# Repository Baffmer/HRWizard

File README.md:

# HRWizard
Projekt "HRWizard" für das Modul "Eingebettete Systeme"

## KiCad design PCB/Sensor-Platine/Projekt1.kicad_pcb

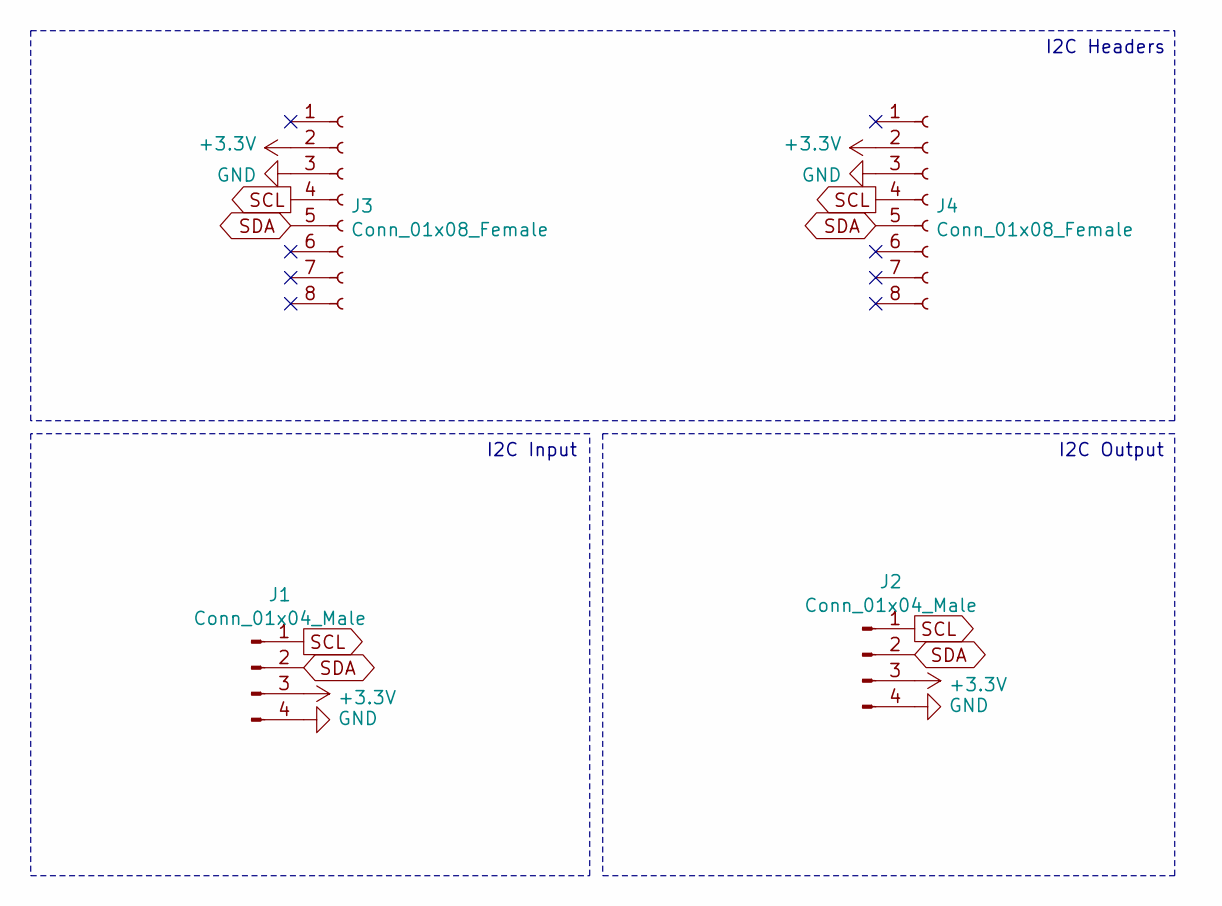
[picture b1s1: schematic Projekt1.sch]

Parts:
J1, J2: Conn_01x04_Male; PinHeader_1x04_P2.00mm_Vertical
J3, J4: Conn_01x08_Female; PinHeader_1x08_P2.54mm_Vertical

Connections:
+3V3: J1.3, J2.3, J3.2, J4.2
GND: J1.4, J2.4, J3.3, J4.3
SCL: J1.1, J2.1, J3.4, J4.4
SDA: J1.2, J2.2, J3.5, J4.5

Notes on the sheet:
I2C Input
I2C Output
I2C Headers

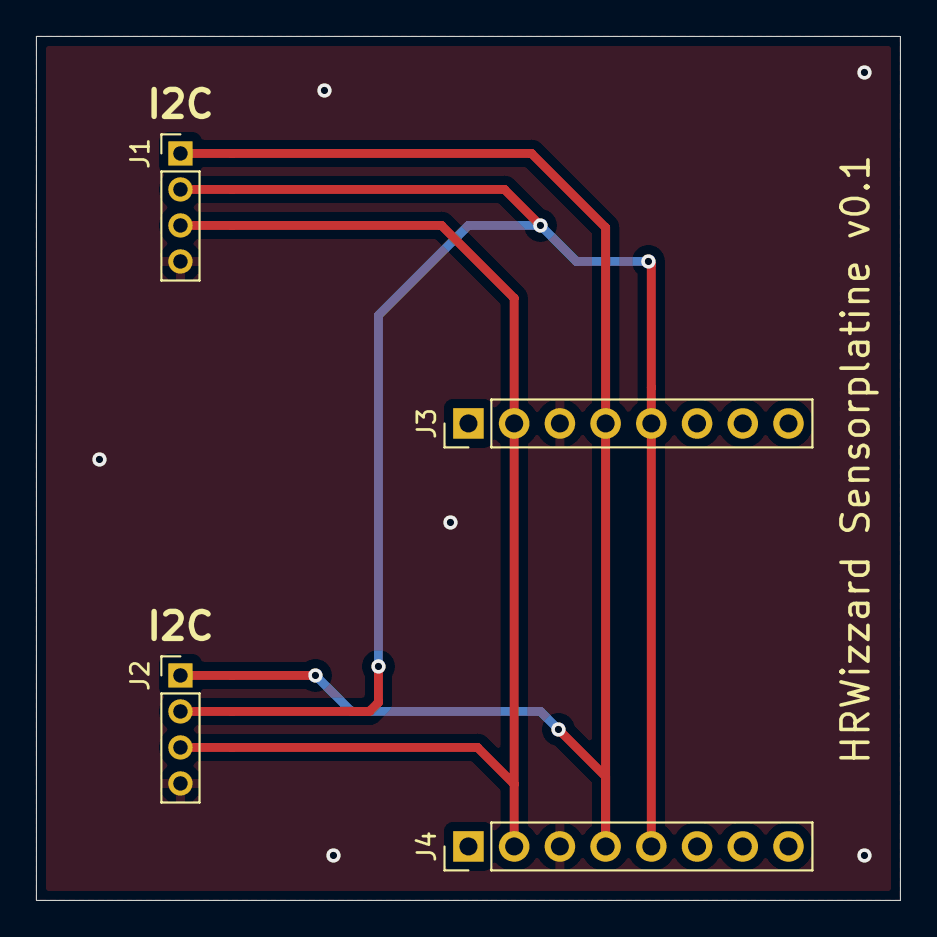
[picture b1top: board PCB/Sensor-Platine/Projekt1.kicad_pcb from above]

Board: 2 copper layers, 48.0 x 48.0 mm, 4 parts (0 on the bottom side), 4 nets.

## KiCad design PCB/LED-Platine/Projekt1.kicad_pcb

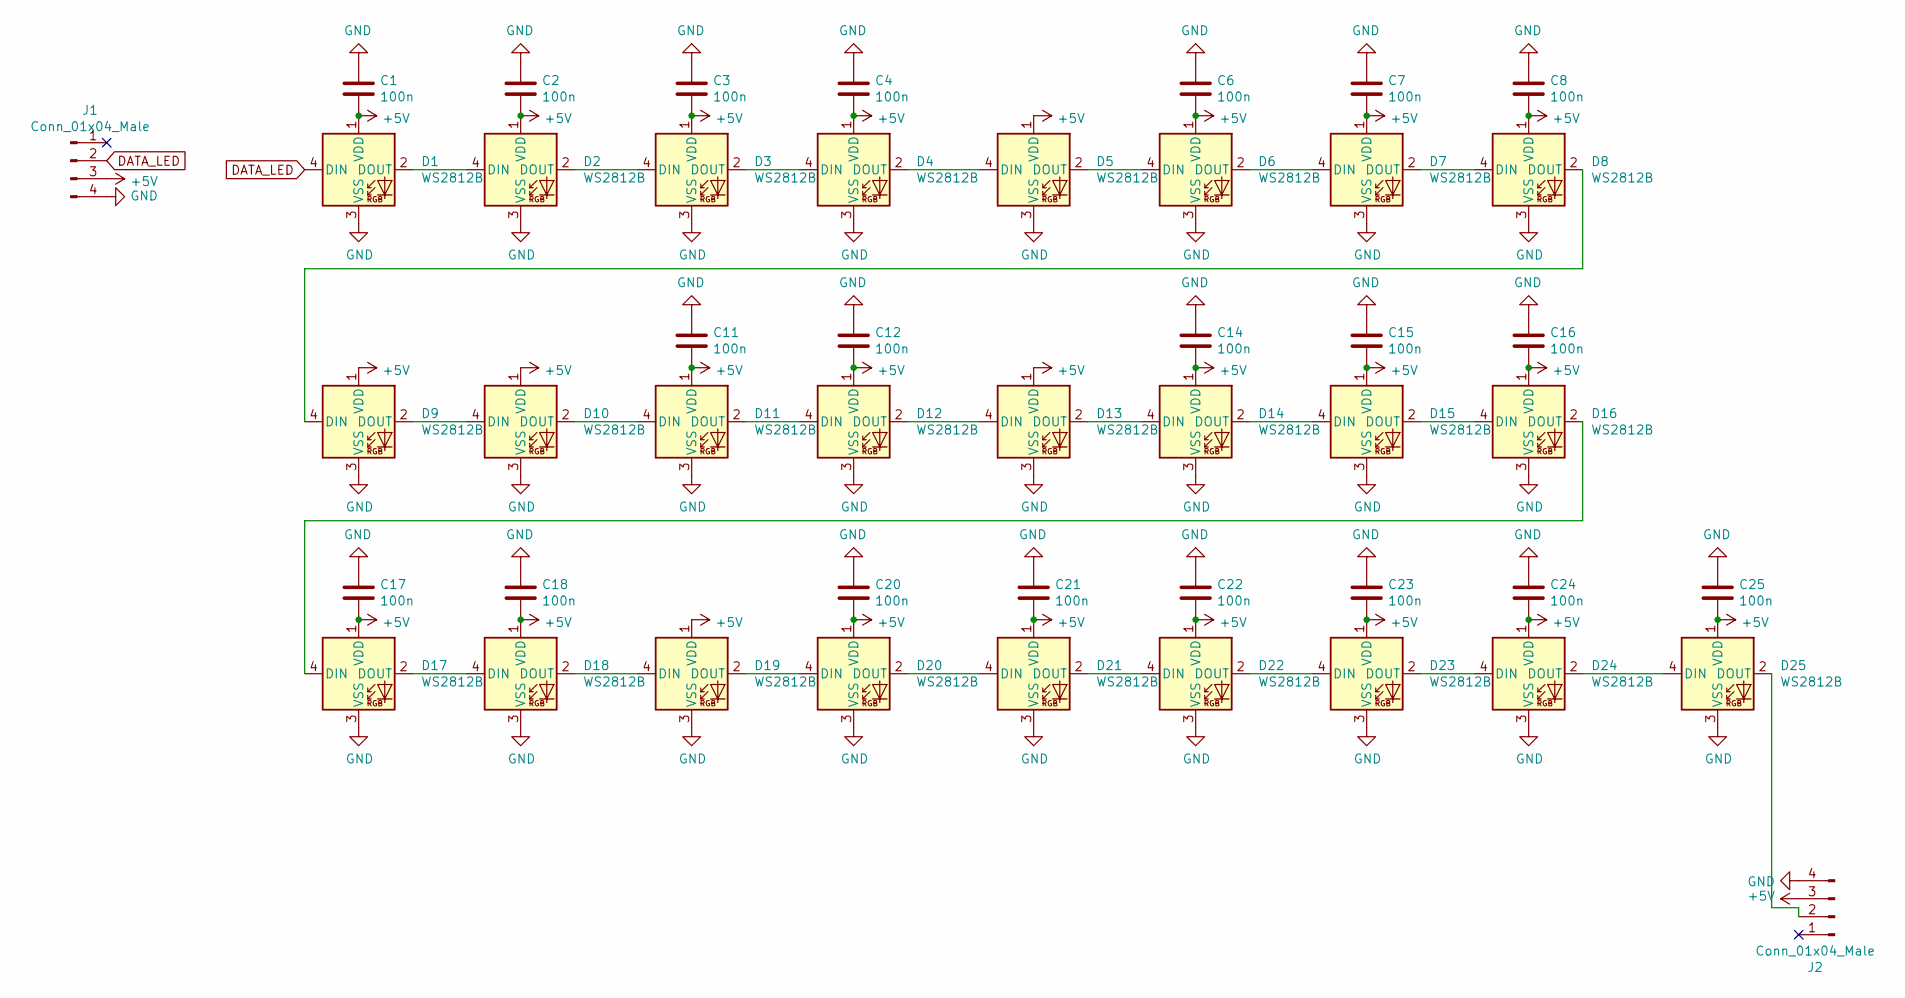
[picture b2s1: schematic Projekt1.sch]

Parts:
C1, C2, C3, C4, C6, C7, C8, C11, C12, C14, C15, C16, C17, C18, C20, C21, C22, C23, C24, C25: 100n; C_0805_2012Metric_Pad1.18x1.45mm_HandSolder
D1, D2, D3, D4, D5, D6, D7, D8, D9, D10, D11, D12, D13, D14, D15, D16, D17, D18, D19, D20, D21, D22, D23, D24, D25: WS2812B; LED_WS2812B_PLCC4_5.0x5.0mm_P3.2mm
J1, J2: Conn_01x04_Male; PinHeader_1x04_P2.00mm_Vertical

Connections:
+5V: C1.1, C2.1, C3.1, C4.1, C6.1, C7.1, C8.1, C11.1, C12.1, C14.1, C15.1, C16.1, C17.1, C18.1, C20.1, C21.1, C22.1, C23.1, C24.1, C25.1, D1.1 (VDD), D2.1 (VDD), D3.1 (VDD), D4.1 (VDD), D5.1 (VDD), D6.1 (VDD), D7.1 (VDD), D8.1 (VDD), D9.1 (VDD), D10.1 (VDD), D11.1 (VDD), D12.1 (VDD), D13.1 (VDD), D14.1 (VDD), D15.1 (VDD), D16.1 (VDD), D17.1 (VDD), D18.1 (VDD), D19.1 (VDD), D20.1 (VDD), D21.1 (VDD), D22.1 (VDD), D23.1 (VDD), D24.1 (VDD), D25.1 (VDD), J1.3, J2.3
DATA_LED: D1.4 (DIN), J1.2
GND: C1.2, C2.2, C3.2, C4.2, C6.2, C7.2, C8.2, C11.2, C12.2, C14.2, C15.2, C16.2, C17.2, C18.2, C20.2, C21.2, C22.2, C23.2, C24.2, C25.2, D1.3 (VSS), D2.3 (VSS), D3.3 (VSS), D4.3 (VSS), D5.3 (VSS), D6.3 (VSS), D7.3 (VSS), D8.3 (VSS), D9.3 (VSS), D10.3 (VSS), D11.3 (VSS), D12.3 (VSS), D13.3 (VSS), D14.3 (VSS), D15.3 (VSS), D16.3 (VSS), D17.3 (VSS), D18.3 (VSS), D19.3 (VSS), D20.3 (VSS), D21.3 (VSS), D22.3 (VSS), D23.3 (VSS), D24.3 (VSS), D25.3 (VSS), J1.4, J2.4
unnamed: D1.2 (DOUT), D2.4 (DIN)
unnamed: D2.2 (DOUT), D3.4 (DIN)
unnamed: D3.2 (DOUT), D4.4 (DIN)
unnamed: D4.2 (DOUT), D5.4 (DIN)
unnamed: D5.2 (DOUT), D6.4 (DIN)
unnamed: D6.2 (DOUT), D7.4 (DIN)
unnamed: D7.2 (DOUT), D8.4 (DIN)
unnamed: D8.2 (DOUT), D9.4 (DIN)
unnamed: D10.2 (DOUT), D11.4 (DIN)
unnamed: D9.2 (DOUT), D10.4 (DIN)
unnamed: D11.2 (DOUT), D12.4 (DIN)
unnamed: D12.2 (DOUT), D13.4 (DIN)
unnamed: D13.2 (DOUT), D14.4 (DIN)
unnamed: D14.2 (DOUT), D15.4 (DIN)
unnamed: D15.2 (DOUT), D16.4 (DIN)
unnamed: D16.2 (DOUT), D17.4 (DIN)
unnamed: D17.2 (DOUT), D18.4 (DIN)
unnamed: D18.2 (DOUT), D19.4 (DIN)
unnamed: D19.2 (DOUT), D20.4 (DIN)
unnamed: D20.2 (DOUT), D21.4 (DIN)
unnamed: D21.2 (DOUT), D22.4 (DIN)
unnamed: D22.2 (DOUT), D23.4 (DIN)
unnamed: D23.2 (DOUT), D24.4 (DIN)
unnamed: D24.2 (DOUT), D25.4 (DIN)
unnamed: D25.2 (DOUT), J2.2

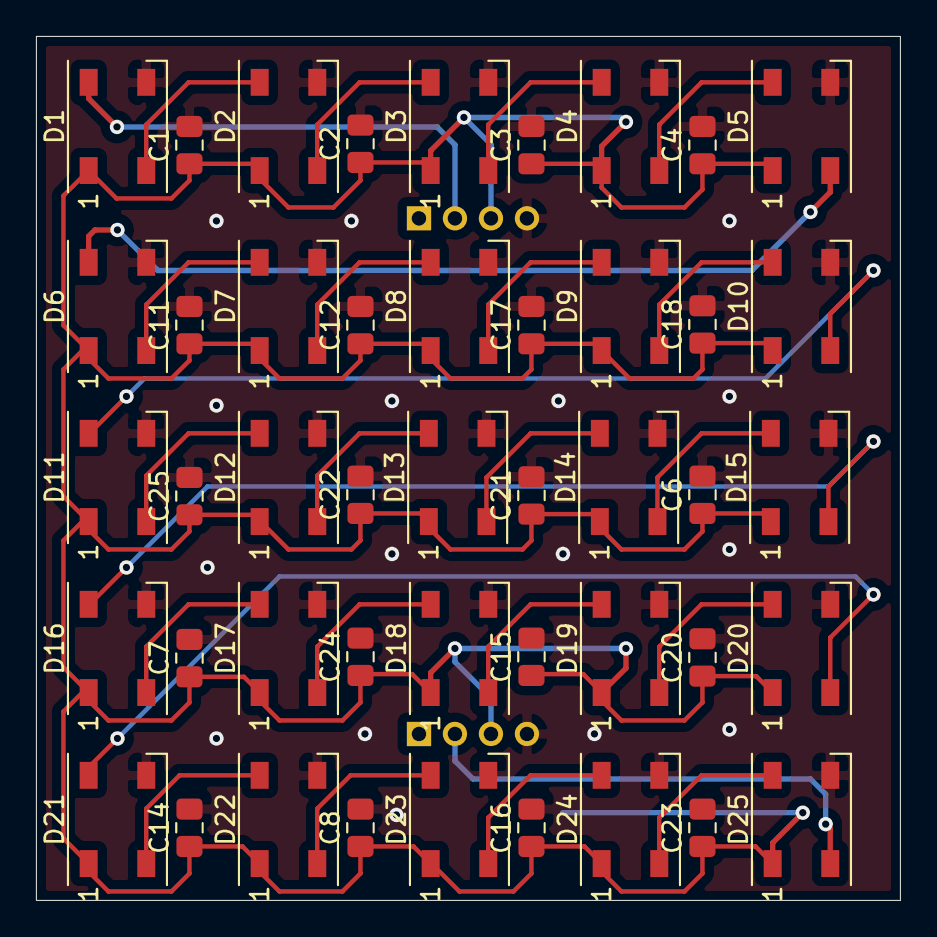
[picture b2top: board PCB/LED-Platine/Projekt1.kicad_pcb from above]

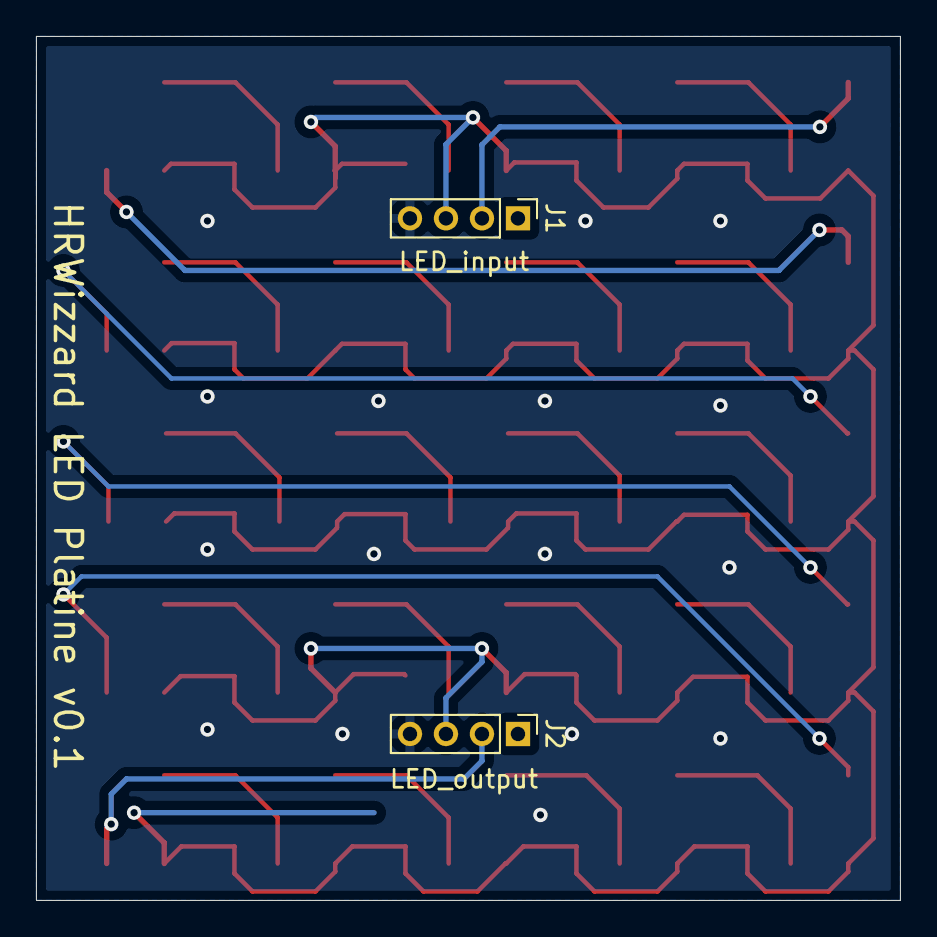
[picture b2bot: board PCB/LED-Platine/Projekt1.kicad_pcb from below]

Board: 2 copper layers, 48.0 x 48.0 mm, 47 parts (2 on the bottom side), 28 nets.

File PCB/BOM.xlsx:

Name | MPN | Placed | References | Value | Quantity PCB | Quantity | Price Per Piece | Price
Seeed Studio Zubehör Grove - Universal 4 pin connector | 110990030 | yes | Grove Stecker | Grove_Connector | 3 | 7 | 0.127 | 2.6669999999999998
Female Pin Header für Sensoren | M20-7820842 | yes | Sensorplatine | Conn_01x08_Female | 3 | 2 | 0.88900000000000001 | 5.3339999999999996
Pufferkondensator für LEDs | CC0805KRX7R9BB104 | yes | C1, C2, C3, C4, C6, C7, C8, C11, C12, C14, C15, C16, C17, C18, C20, C21, C22, C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 | 0805 - 100n | 3 | 20 | 3.3000000000000002E-2 | 1.98
RGB LEDs | COM-16346 | yes | D1, D2, D3, D4, D5, D6, D7, D8, D9, D10, D11, D12, D13, D14, D15, D16, D17, D18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 | WS2812B | 3 | 25 | 0.44040000000000001 | 33.03
Vorwiderstand Power LED | CRCW0805330RFKTA | yes | R9 | 0805 - 330R | 3 | 1 | 0.108 | 0.32400000000000001
Power LED orange | HSMD-C170 | yes | D1 | LED_Small | 3 | 1 | 0.219 | 0.65700000000000003
Raspberry Pi Pico | DEV-17829 | yes | U1 | Pico | 3 | 1 | 4.29 | 12.870000000000001
Tactical Switch | TS04-66-95-BK-260-SMT | yes | SW1, SW2, SW3, SW4, SW5, SW6, SW7 | SW_Push | 3 | 7 | 0.14699999999999999 | 3.0869999999999997
Seeed Grove Cable | 114991495 |  |  |  | 1 | 20 | 0.47 | 9.3999999999999986
 |  |  |  |  |  |  | Gesamt: | 69.349000000000018

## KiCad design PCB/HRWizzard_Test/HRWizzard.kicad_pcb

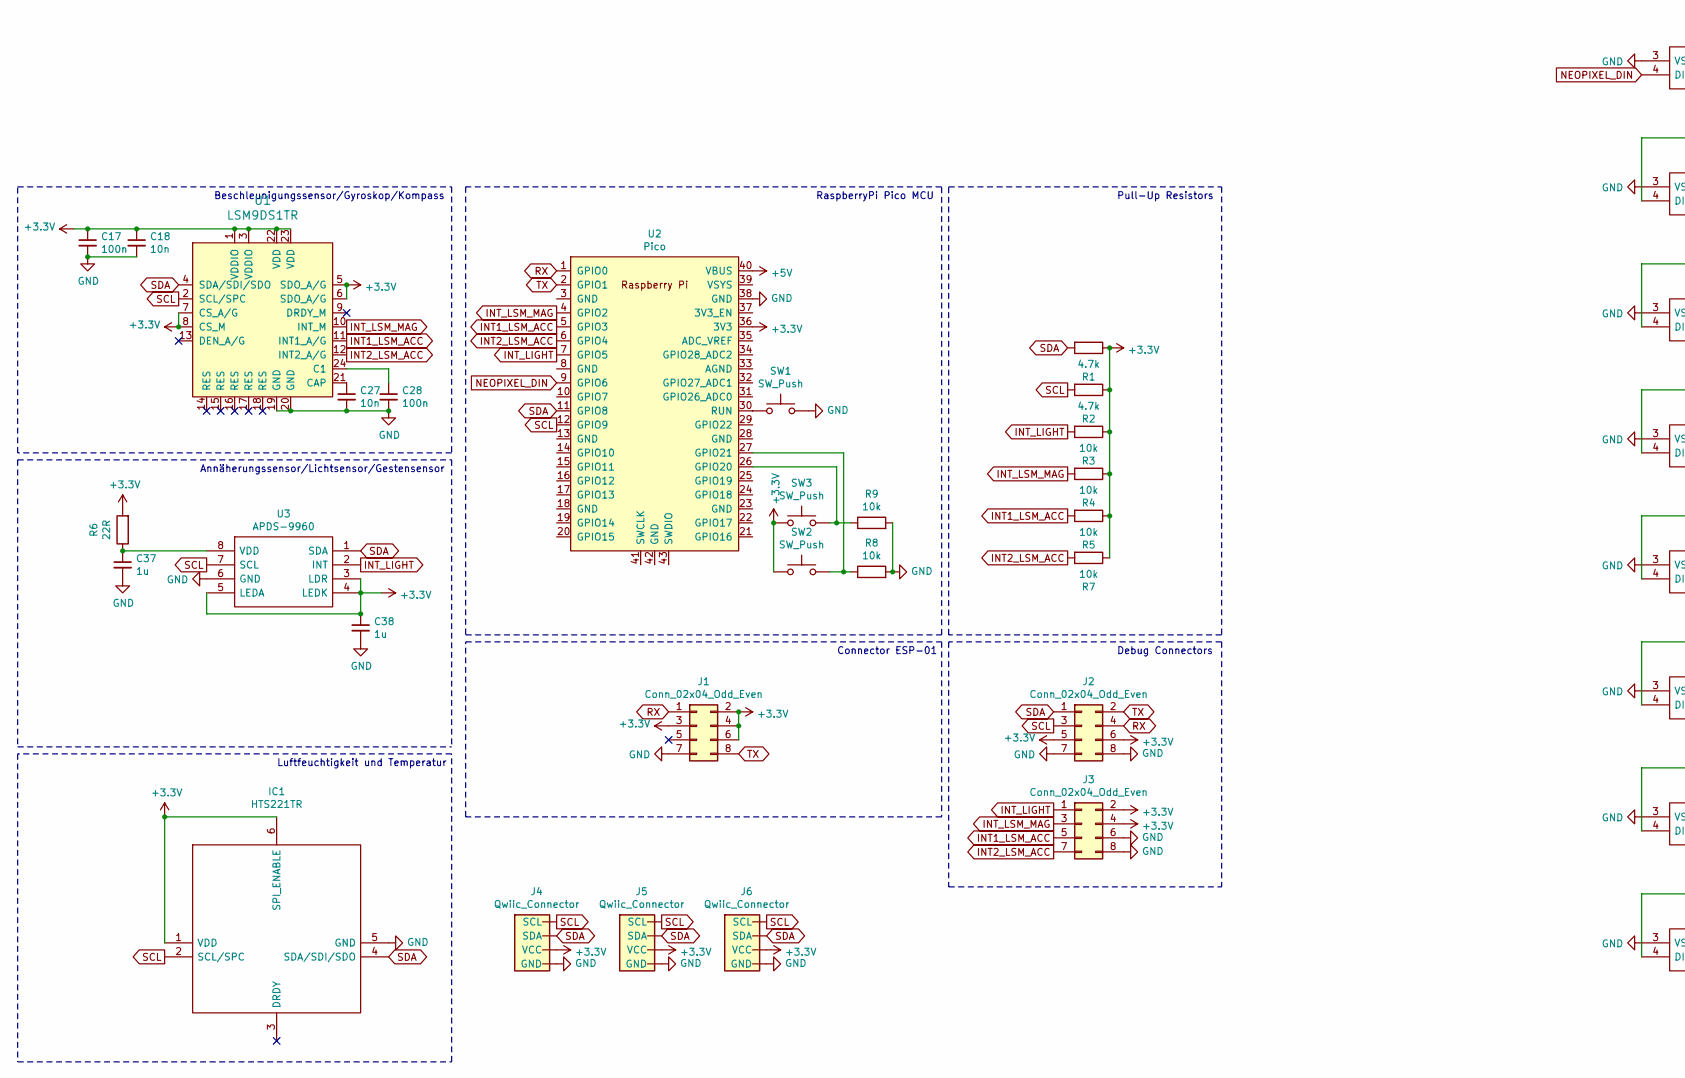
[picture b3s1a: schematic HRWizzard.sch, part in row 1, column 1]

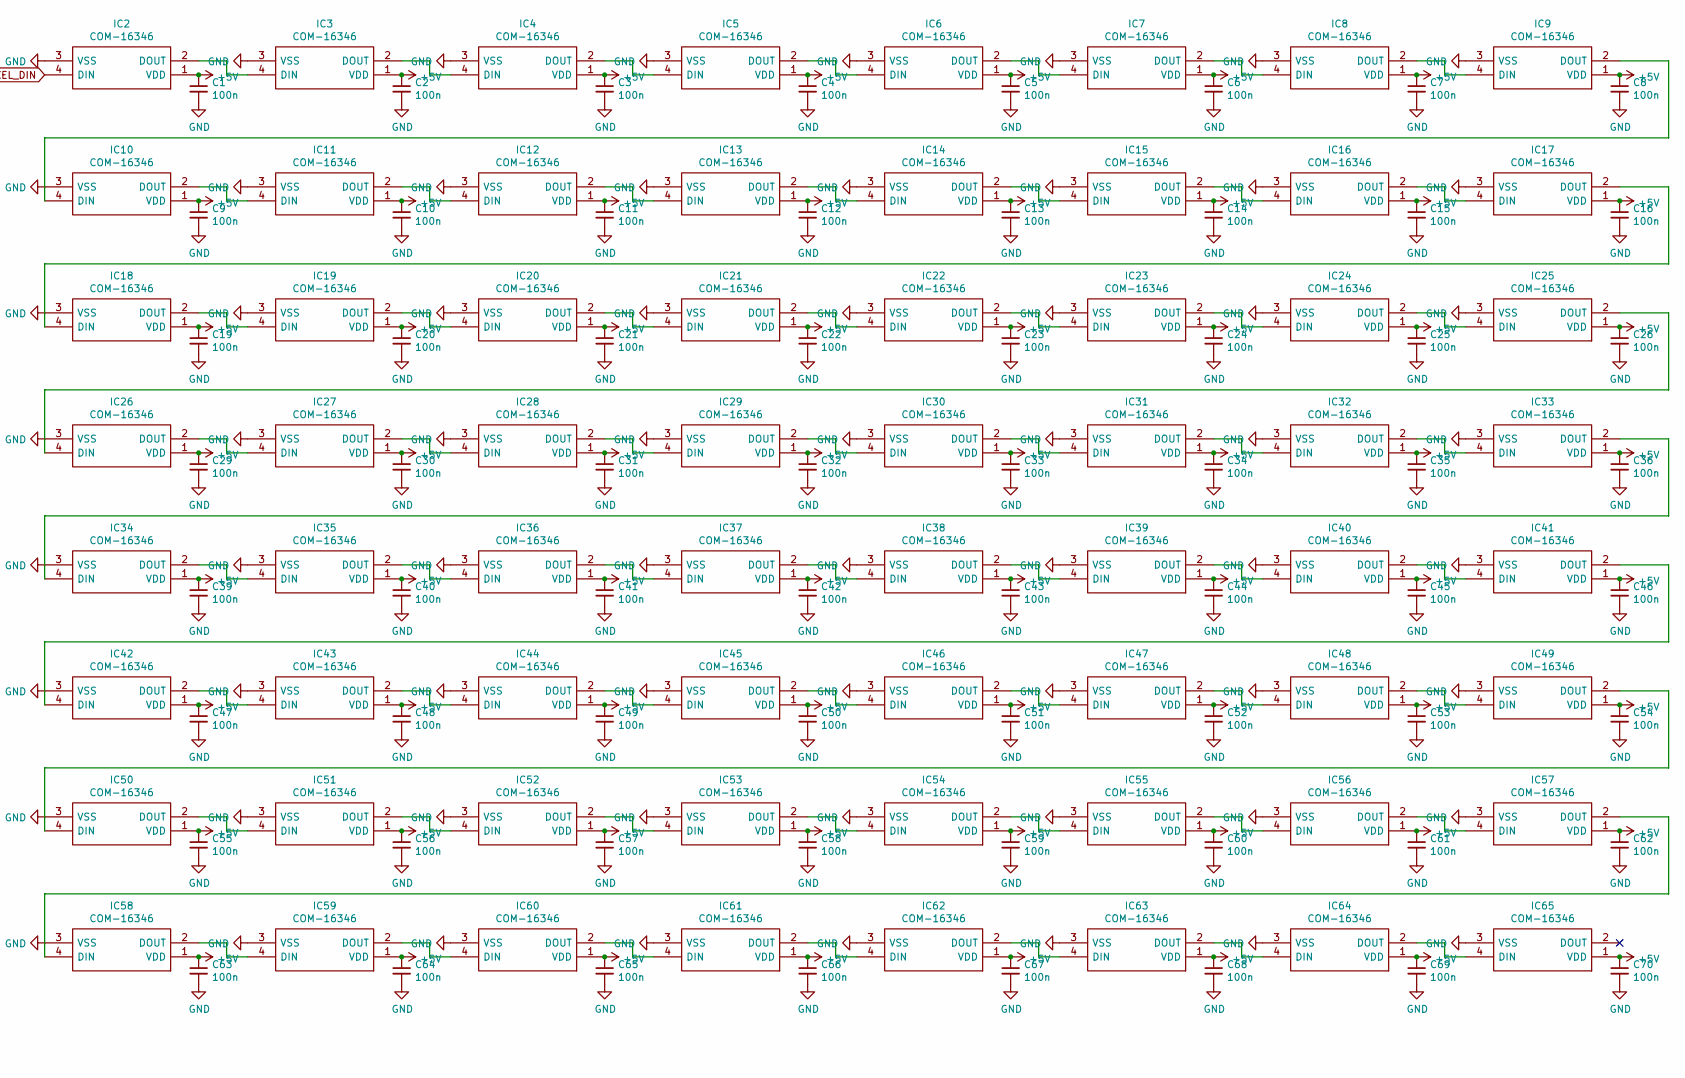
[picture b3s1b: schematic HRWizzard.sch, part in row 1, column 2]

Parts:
C1, C2, C3, C4, C5, C6, C7, C8, C9, C10, C11, C12, C13, C14, C15, C16, C17, C19, C20, C21, C22, C23, C24, C25, C26, C28, C29, C30, C31, C32, C33, C34, C35, C36, C39, C40, C41, C42, C43, C44, C45, C46, C47, C48, C49, C50, C51, C52, C53, C54, C55, C56, C57, C58, C59, C60, C61, C62, C63, C64, C65, C66, C67, C68, C69, C70: 100n; C_0805_2012Metric_Pad1.18x1.45mm_HandSolder
C18, C27: 10n; C_0805_2012Metric_Pad1.18x1.45mm_HandSolder
C37, C38: 1u; C_0805_2012Metric_Pad1.18x1.45mm_HandSolder
IC1: HTS221TR; HLGA-6L; Manufacturer_Part_Number HTS221TR; Mouser Part Number 511-HTS221TR
IC2, IC3, IC4, IC5, IC6, IC7, IC8, IC9, IC10, IC11, IC12, IC13, IC14, IC15, IC16, IC17, IC18, IC19, IC20, IC21, IC22, IC23, IC24, IC25, IC26, IC27, IC28, IC29, IC30, IC31, IC32, IC33, IC34, IC35, IC36, IC37, IC38, IC39, IC40, IC41, IC42, IC43, IC44, IC45, IC46, IC47, IC48, IC49, IC50, IC51, IC52, IC53, IC54, IC55, IC56, IC57, IC58, IC59, IC60, IC61, IC62, IC63, IC64, IC65: COM-16346; COM16346; Manufacturer_Part_Number COM-16346; Mouser Part Number 474-COM-16346
J1, J2, J3: Conn_02x04_Odd_Even; PinHeader_2x04_P2.54mm_Vertical
J4, J5, J6: Qwiic_Connector; JST_GH_SM04B-GHS-TB_1x04-1MP_P1.25mm_Horizontal
R1, R2: 4.7k; R_0805_2012Metric_Pad1.20x1.40mm_HandSolder
R3, R4, R5, R7, R8, R9: 10k; R_0805_2012Metric_Pad1.20x1.40mm_HandSolder
R6: 22R; R_0805_2012Metric_Pad1.20x1.40mm_HandSolder
SW1, SW2, SW3: SW_Push; Switch_Tactile_SMD_6x6mm
U1: LSM9DS1TR; LGA-24_3x3.5mm_LSM9DS1; MPN LSM9DS1TR; Digi-Key_PN 497-14946-1-ND
U2: Pico; RPi_Pico_SMD_TH
U3: APDS-9960; APDS-9950; Manufacturer_Part_Number APDS-9960; Mouser Part Number 630-APDS-9960

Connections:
+3V3: C17.1, C18.1, C38.1, IC1.1 (VDD), IC1.6 (SPI_ENABLE), J1.2, J1.3, J1.4, J1.6, J2.5, J2.6, J3.2, J3.4, J4.2 (VCC), J5.2 (VCC), J6.2 (VCC), R1.1, R2.1, R3.1, R4.1, R5.1, R6.2, R7.1, SW2.1, SW3.1, U1.1 (VDDIO), U1.3 (VDDIO), U1.5 (SDO_A/G), U1.6 (SDO_A/G), U1.7 (CS_A/G), U1.8 (CS_M), U1.22 (VDD), U1.23 (VDD), U2.36 (3V3), U3.3 (LDR), U3.4 (LEDK), U3.5 (LEDA)
+5V: C1.1, C2.1, C3.1, C4.1, C5.1, C6.1, C7.1, C8.1, C9.1, C10.1, C11.1, C12.1, C13.1, C14.1, C15.1, C16.1, C19.1, C20.1, C21.1, C22.1, C23.1, C24.1, C25.1, C26.1, C29.1, C30.1, C31.1, C32.1, C33.1, C34.1, C35.1, C36.1, C39.1, C40.1, C41.1, C42.1, C43.1, C44.1, C45.1, C46.1, C47.1, C48.1, C49.1, C50.1, C51.1, C52.1, C53.1, C54.1, C55.1, C56.1, C57.1, C58.1, C59.1, C60.1, C61.1, C62.1, C63.1, C64.1, C65.1, C66.1, C67.1, C68.1, C69.1, C70.1, IC2.1 (VDD), IC3.1 (VDD), IC4.1 (VDD), IC5.1 (VDD), IC6.1 (VDD), IC7.1 (VDD), IC8.1 (VDD), IC9.1 (VDD), IC10.1 (VDD), IC11.1 (VDD), IC12.1 (VDD), IC13.1 (VDD), IC14.1 (VDD), IC15.1 (VDD), IC16.1 (VDD), IC17.1 (VDD), IC18.1 (VDD), IC19.1 (VDD), IC20.1 (VDD), IC21.1 (VDD), IC22.1 (VDD), IC23.1 (VDD), IC24.1 (VDD), IC25.1 (VDD), IC26.1 (VDD), IC27.1 (VDD), IC28.1 (VDD), IC29.1 (VDD), IC30.1 (VDD), IC31.1 (VDD), IC32.1 (VDD), IC33.1 (VDD), IC34.1 (VDD), IC35.1 (VDD), IC36.1 (VDD), IC37.1 (VDD), IC38.1 (VDD), IC39.1 (VDD), IC40.1 (VDD), IC41.1 (VDD), IC42.1 (VDD), IC43.1 (VDD), IC44.1 (VDD), IC45.1 (VDD), IC46.1 (VDD), IC47.1 (VDD), IC48.1 (VDD), IC49.1 (VDD), IC50.1 (VDD), IC51.1 (VDD), IC52.1 (VDD), IC53.1 (VDD), IC54.1 (VDD), IC55.1 (VDD), IC56.1 (VDD), IC57.1 (VDD), IC58.1 (VDD), IC59.1 (VDD), IC60.1 (VDD), IC61.1 (VDD), IC62.1 (VDD), IC63.1 (VDD), IC64.1 (VDD), IC65.1 (VDD), U2.40 (VBUS)
INT1_LSM_ACC: J3.5, R5.2, U1.11 (INT1_A/G), U2.5 (GPIO3)
INT2_LSM_ACC: J3.7, R7.2, U1.12 (INT2_A/G), U2.6 (GPIO4)
INT_LIGHT: J3.1, R3.2, U2.7 (GPIO5), U3.2 (INT)
INT_LSM_MAG: J3.3, R4.2, U1.10 (INT_M), U2.4 (GPIO2)
NEOPIXEL_DIN: IC2.4 (DIN), U2.9 (GPIO6)
unnamed: C27.1, U1.21 (CAP)
unnamed: C28.1, U1.24 (C1)
unnamed: C37.1, R6.1, U3.8 (VDD)
unnamed: IC2.2 (DOUT), IC3.4 (DIN)
unnamed: IC3.2 (DOUT), IC4.4 (DIN)
unnamed: IC4.2 (DOUT), IC5.4 (DIN)
unnamed: IC5.2 (DOUT), IC6.4 (DIN)
unnamed: IC6.2 (DOUT), IC7.4 (DIN)
unnamed: IC7.2 (DOUT), IC8.4 (DIN)
unnamed: IC8.2 (DOUT), IC9.4 (DIN)
unnamed: IC10.2 (DOUT), IC11.4 (DIN)
unnamed: IC11.2 (DOUT), IC12.4 (DIN)
unnamed: IC12.2 (DOUT), IC13.4 (DIN)
unnamed: IC13.2 (DOUT), IC14.4 (DIN)
unnamed: IC14.2 (DOUT), IC15.4 (DIN)
unnamed: IC15.2 (DOUT), IC16.4 (DIN)
unnamed: IC16.2 (DOUT), IC17.4 (DIN)
unnamed: IC18.2 (DOUT), IC19.4 (DIN)
unnamed: IC19.2 (DOUT), IC20.4 (DIN)
unnamed: IC20.2 (DOUT), IC21.4 (DIN)
unnamed: IC21.2 (DOUT), IC22.4 (DIN)
unnamed: IC22.2 (DOUT), IC23.4 (DIN)
unnamed: IC23.2 (DOUT), IC24.4 (DIN)
unnamed: IC24.2 (DOUT), IC25.4 (DIN)
unnamed: IC26.2 (DOUT), IC27.4 (DIN)
unnamed: IC27.2 (DOUT), IC28.4 (DIN)
unnamed: IC28.2 (DOUT), IC29.4 (DIN)
unnamed: IC29.2 (DOUT), IC30.4 (DIN)
unnamed: IC30.2 (DOUT), IC31.4 (DIN)
unnamed: IC31.2 (DOUT), IC32.4 (DIN)
unnamed: IC32.2 (DOUT), IC33.4 (DIN)
unnamed: IC34.2 (DOUT), IC35.4 (DIN)
unnamed: IC35.2 (DOUT), IC36.4 (DIN)
unnamed: IC36.2 (DOUT), IC37.4 (DIN)
unnamed: IC37.2 (DOUT), IC38.4 (DIN)
unnamed: IC38.2 (DOUT), IC39.4 (DIN)
unnamed: IC39.2 (DOUT), IC40.4 (DIN)
unnamed: IC40.2 (DOUT), IC41.4 (DIN)
unnamed: IC42.2 (DOUT), IC43.4 (DIN)
unnamed: IC43.2 (DOUT), IC44.4 (DIN)
unnamed: IC44.2 (DOUT), IC45.4 (DIN)
unnamed: IC45.2 (DOUT), IC46.4 (DIN)
unnamed: IC46.2 (DOUT), IC47.4 (DIN)
unnamed: IC47.2 (DOUT), IC48.4 (DIN)
unnamed: IC48.2 (DOUT), IC49.4 (DIN)
unnamed: IC50.2 (DOUT), IC51.4 (DIN)
unnamed: IC51.2 (DOUT), IC52.4 (DIN)
unnamed: IC52.2 (DOUT), IC53.4 (DIN)
unnamed: IC53.2 (DOUT), IC54.4 (DIN)
unnamed: IC54.2 (DOUT), IC55.4 (DIN)
unnamed: IC55.2 (DOUT), IC56.4 (DIN)
unnamed: IC56.2 (DOUT), IC57.4 (DIN)
unnamed: IC58.2 (DOUT), IC59.4 (DIN)
unnamed: IC59.2 (DOUT), IC60.4 (DIN)
unnamed: IC60.2 (DOUT), IC61.4 (DIN)
unnamed: IC61.2 (DOUT), IC62.4 (DIN)
unnamed: IC62.2 (DOUT), IC63.4 (DIN)
unnamed: IC63.2 (DOUT), IC64.4 (DIN)
unnamed: IC64.2 (DOUT), IC65.4 (DIN)
unnamed: R8.1, SW2.2, U2.27 (GPIO21)
unnamed: R9.1, SW3.2, U2.26 (GPIO20)
unnamed: SW1.1, U2.30 (RUN)
RX: J1.1, J2.4, U2.1 (GPIO0)
SCL: IC1.2 (SCL/SPC), J2.3, J4.4 (SCL), J5.4 (SCL), J6.4 (SCL), R2.2, U1.2 (SCL/SPC), U2.12 (GPIO9), U3.7 (SCL)
SDA: IC1.4 (SDA/SDI/SDO), J2.1, J4.3 (SDA), J5.3 (SDA), J6.3 (SDA), R1.2, U1.4 (SDA/SDI/SDO), U2.11 (GPIO8), U3.1 (SDA)
TX: J1.8, J2.2, U2.2 (GPIO1)

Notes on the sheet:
Annäherungssensor/Lichtsensor/Gestensensor
Beschleunigungssensor/Gyroskop/Kompass
Luftfeuchtigkeit und Temperatur
Pull-Up Resistors
RaspberryPi Pico MCU
Connector ESP-01
Debug Connectors

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
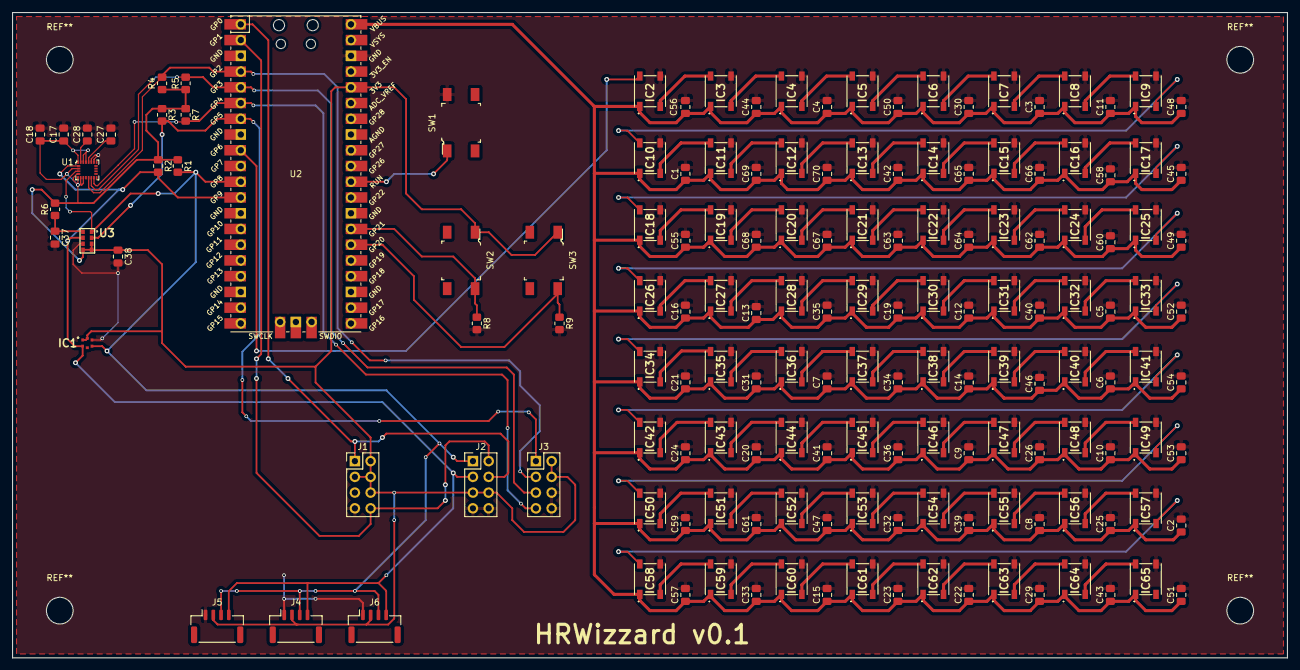
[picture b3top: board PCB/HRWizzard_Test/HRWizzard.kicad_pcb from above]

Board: 2 copper layers, 205.7 x 104.1 mm, 156 parts (0 on the bottom side), 81 nets.

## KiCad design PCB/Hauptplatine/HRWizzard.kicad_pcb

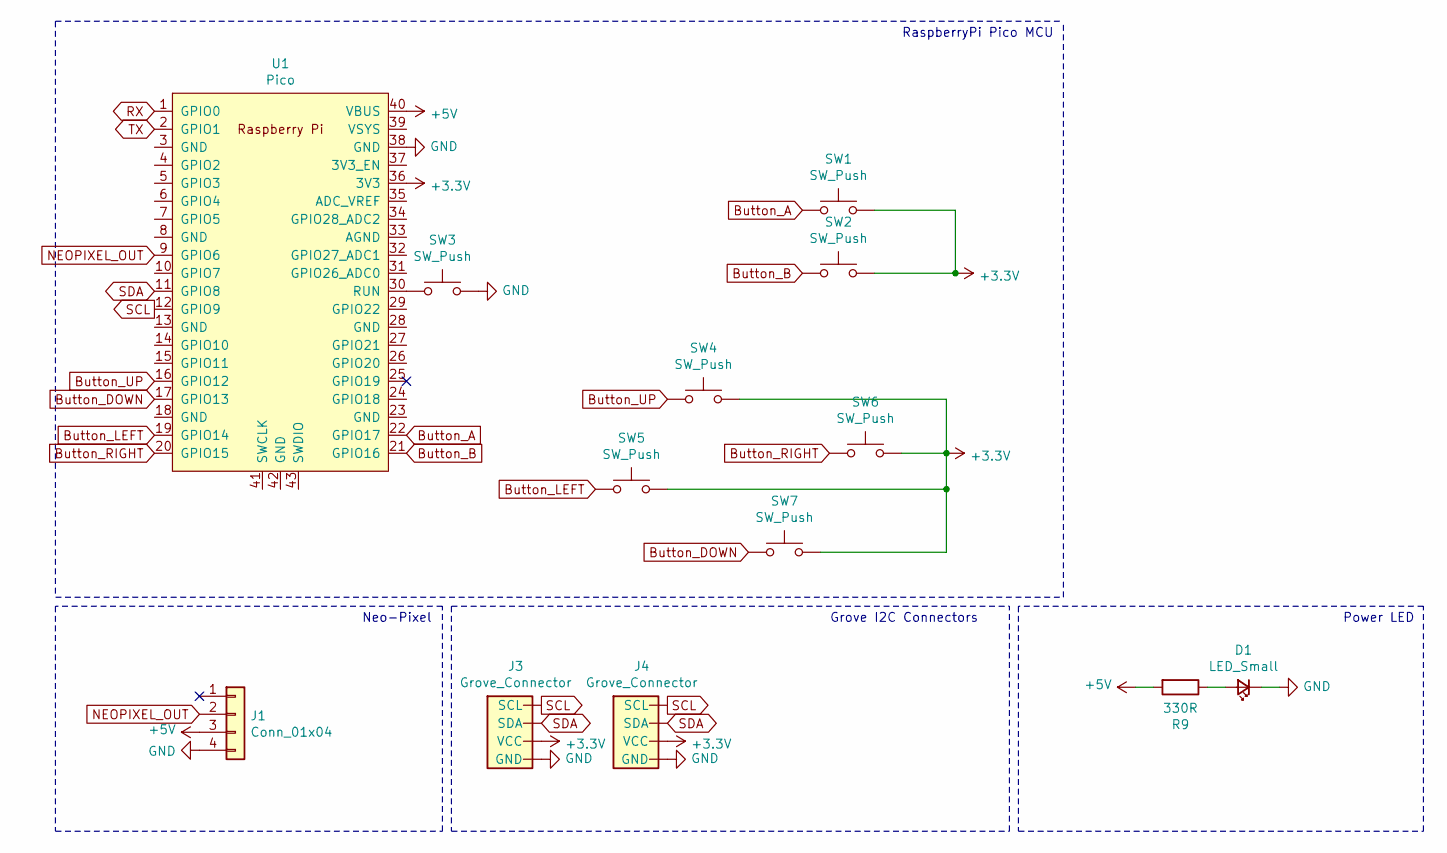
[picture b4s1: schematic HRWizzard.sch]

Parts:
D1: LED_Small; LED_0805_2012Metric_Pad1.15x1.40mm_HandSolder
J1: Conn_01x04; PinHeader_1x04_P2.00mm_Vertical
J3, J4: Grove_Connector; PinHeader_1x04_P2.00mm_Vertical
R9: 330R; R_0805_2012Metric_Pad1.20x1.40mm_HandSolder
SW1, SW2, SW3, SW4, SW5, SW6, SW7: SW_Push; Switch_Tactile_SMD_6x6mm
U1: Pico; RPi_Pico_SMD_TH

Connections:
+3V3: J3.2 (VCC), J4.2 (VCC), SW1.2, SW2.2, SW4.2, SW5.2, SW6.2, SW7.2, U1.36 (3V3)
+5V: J1.3, R9.2, U1.40 (VBUS)
Button_A: SW1.1, U1.22 (GPIO17)
Button_B: SW2.1, U1.21 (GPIO16)
Button_DOWN: SW7.1, U1.17 (GPIO13)
Button_LEFT: SW5.1, U1.19 (GPIO14)
Button_RIGHT: SW6.1, U1.20 (GPIO15)
Button_UP: SW4.1, U1.16 (GPIO12)
GND: D1.1 (K), J1.4, J3.1 (GND), J4.1 (GND), SW3.2, U1.38 (GND)
NEOPIXEL_OUT: J1.2, U1.9 (GPIO6)
unnamed: D1.2 (A), R9.1
unnamed: SW3.1, U1.30 (RUN)
RX: U1.1 (GPIO0)
SCL: J3.4 (SCL), J4.4 (SCL), U1.12 (GPIO9)
SDA: J3.3 (SDA), J4.3 (SDA), U1.11 (GPIO8)
TX: U1.2 (GPIO1)

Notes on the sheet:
RaspberryPi Pico MCU
Neo-Pixel
Grove I2C Connectors
Power LED

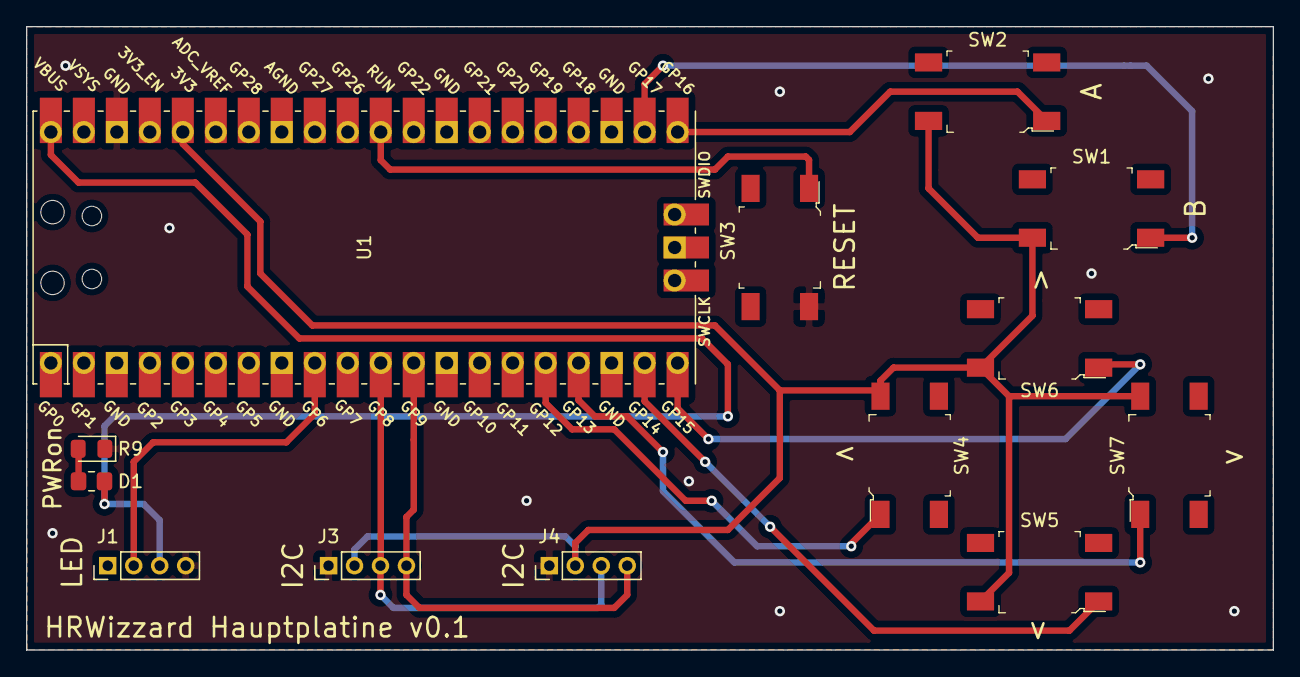
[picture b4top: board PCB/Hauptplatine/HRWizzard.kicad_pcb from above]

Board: 2 copper layers, 96.0 x 48.0 mm, 13 parts (0 on the bottom side), 14 nets.

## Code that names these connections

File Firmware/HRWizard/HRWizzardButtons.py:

import machine
from machine import Timer

def buttonHandler(button):
    ...
    
# Buttons deklarieren
BUTTON_UP =    machine.Pin(12, machine.Pin.IN, machine.Pin.PULL_DOWN)
BUTTON_DOWN =  machine.Pin(13, machine.Pin.IN, machine.Pin.PULL_DOWN)
BUTTON_LEFT =  machine.Pin(14, machine.Pin.IN, machine.Pin.PULL_DOWN)
BUTTON_RIGHT = machine.Pin(15, machine.Pin.IN, machine.Pin.PULL_DOWN)
BUTTON_A =     machine.Pin(17, machine.Pin.IN, machine.Pin.PULL_DOWN)
BUTTON_B =     machine.Pin(16, machine.Pin.IN, machine.Pin.PULL_DOWN)

# Timer für anti-polling
antiPollingTimer = Timer()
blockButtons = False

def initButtons():
    global BUTTON_A
    global BUTTON_B
    global BUTTON_UP
    global BUTTON_DOWN
    global BUTTON_LEFT
    global BUTTON_RIGHT 
    global antiPollingTimer
    
    BUTTON_A.irq(    trigger = machine.Pin.IRQ_RISING | machine.Pin.IRQ_FALLING, handler = buttonHandler)
    BUTTON_B.irq(    trigger = machine.Pin.IRQ_RISING | machine.Pin.IRQ_FALLING, handler = buttonHandler)
    BUTTON_UP.irq(   trigger = machine.Pin.IRQ_RISING | machine.Pin.IRQ_FALLING, handler = buttonHandler)
    BUTTON_DOWN.irq( trigger = machine.Pin.IRQ_RISING | machine.Pin.IRQ_FALLING, handler = buttonHandler)
    BUTTON_LEFT.irq( trigger = machine.Pin.IRQ_RISING | machine.Pin.IRQ_FALLING, handler = buttonHandler)
    BUTTON_RIGHT.irq(trigger = machine.Pin.IRQ_RISING | machine.Pin.IRQ_FALLING, handler = buttonHandler)
    
    antiPollingTimer.init(callback = antiPollingTimerHandler)

def antiPollingTimerHandler(arg):
    global blockButtons
    blockButtons = False

def buttonHandler(button):
    global antiPollingTimer
    global blockButtons
    
    if not blockButtons:
        
        #print(button)
        
        antiPollingTimer.init(period = 100, mode = Timer.ONE_SHOT, callback = antiPollingTimerHandler)
        blockButtons = True
        
        if button.value() == 1:
            if button == BUTTON_A:
                print("Button A gedrückt")
            elif button == BUTTON_B:
                print("Button B gedrückt")
            elif button == BUTTON_UP:
                print("Button UP gedrückt")
            elif button == BUTTON_DOWN:
                print("Button DOWN gedrückt")
            elif button == BUTTON_LEFT:
                print("Button LEFT gedrückt")
            elif button == BUTTON_RIGHT:
                print("Button RIGHT gedrückt")
            else:
                print("unknow button")
        else:
            if button == BUTTON_A:
                print("Button A losgelassen")
            elif button == BUTTON_B:
                print("Button B losgelassen")
            elif button == BUTTON_UP:
                print("Button UP losgelassen")
            elif button == BUTTON_DOWN:
                print("Button DOWN losgelassen")
            elif button == BUTTON_LEFT:
                print("Button LEFT losgelassen")
            elif button == BUTTON_RIGHT:
                print("Button RIGHT losgelassen")
            else:
                print("unknow button")
            
    else:
        print("Buttons blocked!")

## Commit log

2022-04-24 initial upload for wiki
